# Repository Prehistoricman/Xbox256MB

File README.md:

# Xbox 256MB upgrade mod

Upgrade the original Xbox to quadruple its original RAM size. Why? Because we can. **For advanced modders only!** Understand the risks and drawbacks before attempting.

See [my tutorial on the OGXbox forums](https://www.ogxbox.com/forums/index.php?/topic/19155-256mb-ram-upgrade-release-and-tutorial/) or [Macho Nacho's tutorial on YouTube](https://www.youtube.com/watch?v=R2hvSL30Rlg).

# Xblast OS for RAM testing and flashing

See the [bitbucket downloads](https://bitbucket.org/prehistoricman/lpcmod_os/downloads/) and the [bitbucket readme](https://bitbucket.org/prehistoricman/lpcmod_os/src/master/README.md) for the RAM testing BIOS that lets you check each RAM chip individually.

# BIOS patching

Use Python 3 to run the patcher script BIOS_patcher_256MB.py. This patcher works on X2 and X3 BIOSes. Others not tested. Some BIOSes such as EvoX will run 256MB memory after applying this patch but will not be able to use the extra memory. They require additional patching.

Usage:

    python BIOS_patcher_256MB.py <BIOS file path> [-m] [-d]

The `-m` option will slow the RAM speed to 150MHz from the default of 200MHz. **I have found this is necessary on all my Xboxes to run 256MB stably.** You can recover some lost performance by overclocking the BIOS before applying the 256MB patch using a tool such as XBOverclock.

The `-d` option will attempt to adjust the slew and drive trims for the DQS pin. Try this if the system isn't stable.

This script will produce a patched version of the BIOS with `.patched256` appended to the name.

For example:

    python BIOS_patcher_256MB.py x2.5035.v16plus.137.bin -m

# Interposer PCB

This mod uses 256Mbit memory chips HY5DU573222F-28. They are only available in a BGA package, so we need an interposer to convert it to the Xbox's TQFP footprint.

PCB gerbers appropriate for PCBWay are in the github release.

256Mbit_RAM_interposer_v2_flex is my recommended design. It's intended to be manufactured in flexible PCB to be slim, easy to handle, and have enough outline precision to correctly make the castellated holes at the edge of the PCB. You can try ordering it in rigid fibreglass PCB but many manufacturers won't have the required tolerance on the board outline to avoid ripping the castellations apart.

256Mbit_RAM_interposer_rigidflex is my earlier design where the two inner layers are flexible and extend from the board, becoming pins and mimicing the original TQFP package. **This design suffers from the pins being too weak**: they get micro fractures from bending and therefore lose conductivity. This design would be ideal if the flexible layers could be on the bottom side of the board.

# Theory

This is just extra information for those who seek it.

See my video about this mod: [How I put 256MB of RAM in the original Xbox](https://www.youtube.com/watch?v=1idSEhUT4PM)

In short, we can double the memory from 128MB to 256MB by adding 1 more bit of addressing to the memory array. This is done by adding an additional 'column' since the Xbox is already maxed out on address 'rows'. To enable the use of that extra column bit, we have to write to the DRAM controller register called `NV_PFB_CFG1` in the Xbox's startup code (Xcodes). In the same register, we also have to set the AP pin to A9 to account for the flip of A8 and A9 in the interposer. Why are they flipped in the interposer? Because this DRAM controller unfortunately doesn't properly account for the location of the AP pin within the column address. The RAM chip accepts its column address on A0-A7+A9, skipping the A8 pin because its job is to be the AP pin. Instead, the NV2A uses A8 as the most significant bit in the column address (in 9 columns mode) and thus the function of the AP bit is lost and only half of memory is addressable.

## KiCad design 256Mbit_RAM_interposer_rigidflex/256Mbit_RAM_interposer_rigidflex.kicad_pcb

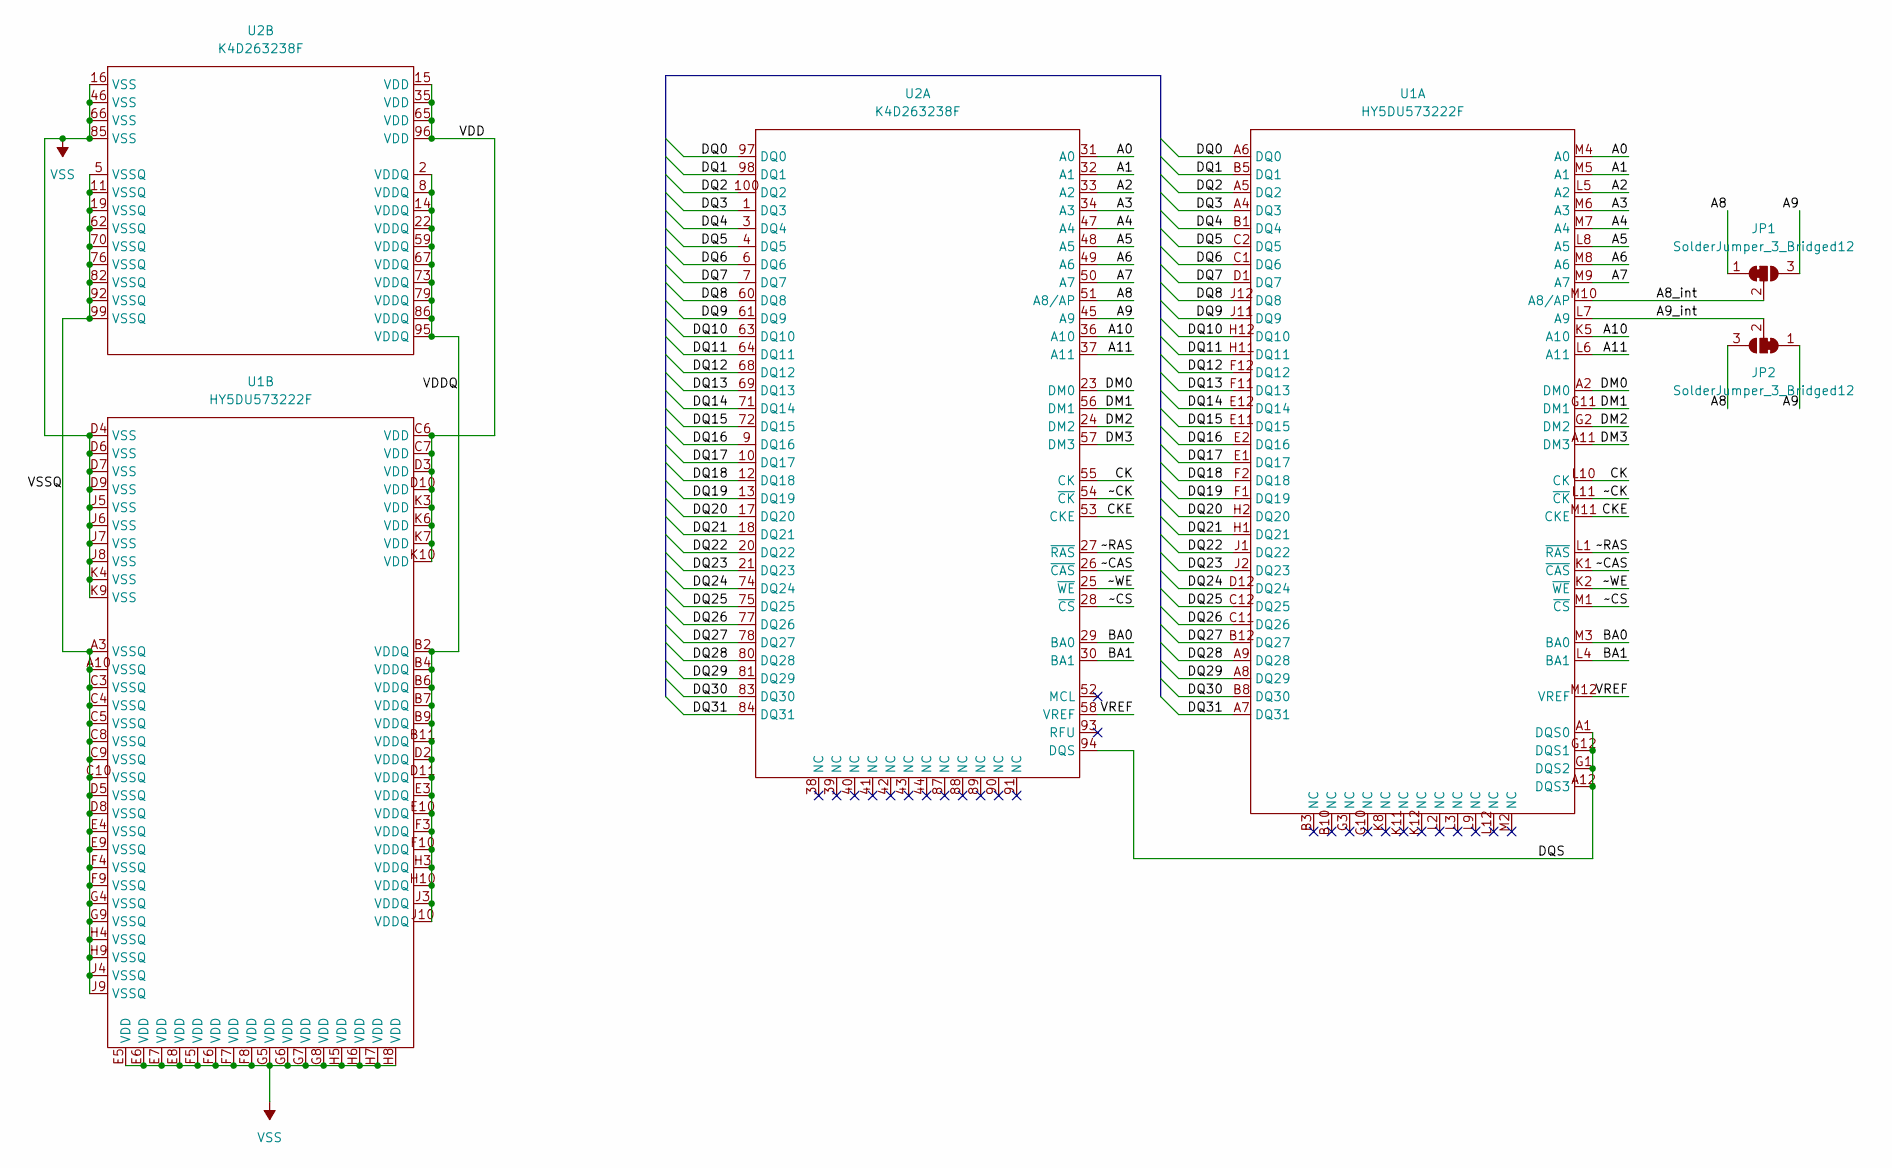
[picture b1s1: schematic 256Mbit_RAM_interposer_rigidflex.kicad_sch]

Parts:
JP1, JP2: SolderJumper_3_Bridged12; SolderJumper-3_P0.8mm_Open
U1: HY5DU573222F; LFBGA-144_10x10mm_Layout12x12_P0.8mm
U2: K4D263238F; PQFP-100_14x20mm_P0.65mm

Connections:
/A0: U1.M4 (A0), U2.31 (A0)
/A1: U1.M5 (A1), U2.32 (A1)
/A2: U1.L5 (A2), U2.33 (A2)
/A3: U1.M6 (A3), U2.34 (A3)
/A4: U1.M7 (A4), U2.47 (A4)
/A5: U1.L8 (A5), U2.48 (A5)
/A6: U1.M8 (A6), U2.49 (A6)
/A7: U1.M9 (A7), U2.50 (A7)
/A8: JP1.1 (A), JP2.3 (B), U2.51 (A8/AP)
/A8_int: JP1.2 (C), U1.M10 (A8/AP)
/A9: JP1.3 (B), JP2.1 (A), U2.45 (A9)
/A9_int: JP2.2 (C), U1.L7 (A9)
/A10: U1.K5 (A10), U2.36 (A10)
/A11: U1.L6 (A11), U2.37 (A11)
/BA0: U1.M3 (BA0), U2.29 (BA0)
/BA1: U1.L4 (BA1), U2.30 (BA1)
/CK: U1.L10 (CK), U2.55 (CK)
/CKE: U1.M11 (CKE), U2.53 (CKE)
/DM0: U1.A2 (DM0), U2.23 (DM0)
/DM1: U1.G11 (DM1), U2.56 (DM1)
/DM2: U1.G2 (DM2), U2.24 (DM2)
/DM3: U1.A11 (DM3), U2.57 (DM3)
/DQ0: U1.A6 (DQ0), U2.97 (DQ0)
/DQ1: U1.B5 (DQ1), U2.98 (DQ1)
/DQ2: U1.A5 (DQ2), U2.100 (DQ2)
/DQ3: U1.A4 (DQ3), U2.1 (DQ3)
/DQ4: U1.B1 (DQ4), U2.3 (DQ4)
/DQ5: U1.C2 (DQ5), U2.4 (DQ5)
/DQ6: U1.C1 (DQ6), U2.6 (DQ6)
/DQ7: U1.D1 (DQ7), U2.7 (DQ7)
/DQ8: U1.J12 (DQ8), U2.60 (DQ8)
/DQ9: U1.J11 (DQ9), U2.61 (DQ9)
/DQ10: U1.H12 (DQ10), U2.63 (DQ10)
/DQ11: U1.H11 (DQ11), U2.64 (DQ11)
/DQ12: U1.F12 (DQ12), U2.68 (DQ12)
/DQ13: U1.F11 (DQ13), U2.69 (DQ13)
/DQ14: U1.E12 (DQ14), U2.71 (DQ14)
/DQ15: U1.E11 (DQ15), U2.72 (DQ15)
/DQ16: U1.E2 (DQ16), U2.9 (DQ16)
/DQ17: U1.E1 (DQ17), U2.10 (DQ17)
/DQ18: U1.F2 (DQ18), U2.12 (DQ18)
/DQ19: U1.F1 (DQ19), U2.13 (DQ19)
/DQ20: U1.H2 (DQ20), U2.17 (DQ20)
/DQ21: U1.H1 (DQ21), U2.18 (DQ21)
/DQ22: U1.J1 (DQ22), U2.20 (DQ22)
/DQ23: U1.J2 (DQ23), U2.21 (DQ23)
/DQ24: U1.D12 (DQ24), U2.74 (DQ24)
/DQ25: U1.C12 (DQ25), U2.75 (DQ25)
/DQ26: U1.C11 (DQ26), U2.77 (DQ26)
/DQ27: U1.B12 (DQ27), U2.78 (DQ27)
/DQ28: U1.A9 (DQ28), U2.80 (DQ28)
/DQ29: U1.A8 (DQ29), U2.81 (DQ29)
/DQ30: U1.B8 (DQ30), U2.83 (DQ30)
/DQ31: U1.A7 (DQ31), U2.84 (DQ31)
/DQS: U1.A1 (DQS0), U1.A12 (DQS3), U1.G1 (DQS2), U1.G12 (DQS1), U2.94 (DQS)
/VDD: U1.C6 (VDD), U1.C7 (VDD), U1.D3 (VDD), U1.D10 (VDD), U1.K3 (VDD), U1.K6 (VDD), U1.K7 (VDD), U1.K10 (VDD), U2.15 (VDD), U2.35 (VDD), U2.65 (VDD), U2.96 (VDD)
/VDDQ: U1.B2 (VDDQ), U1.B4 (VDDQ), U1.B6 (VDDQ), U1.B7 (VDDQ), U1.B9 (VDDQ), U1.B11 (VDDQ), U1.D2 (VDDQ), U1.D11 (VDDQ), U1.E3 (VDDQ), U1.E10 (VDDQ), U1.F3 (VDDQ), U1.F10 (VDDQ), U1.H3 (VDDQ), U1.H10 (VDDQ), U1.J3 (VDDQ), U1.J10 (VDDQ), U2.2 (VDDQ), U2.8 (VDDQ), U2.14 (VDDQ), U2.22 (VDDQ), U2.59 (VDDQ), U2.67 (VDDQ), U2.73 (VDDQ), U2.79 (VDDQ), U2.86 (VDDQ), U2.95 (VDDQ)
/VREF: U1.M12 (VREF), U2.58 (VREF)
/VSSQ: U1.A3 (VSSQ), U1.A10 (VSSQ), U1.C3 (VSSQ), U1.C4 (VSSQ), U1.C5 (VSSQ), U1.C8 (VSSQ), U1.C9 (VSSQ), U1.C10 (VSSQ), U1.D5 (VSSQ), U1.D8 (VSSQ), U1.E4 (VSSQ), U1.E9 (VSSQ), U1.F4 (VSSQ), U1.F9 (VSSQ), U1.G4 (VSSQ), U1.G9 (VSSQ), U1.H4 (VSSQ), U1.H9 (VSSQ), U1.J4 (VSSQ), U1.J9 (VSSQ), U2.5 (VSSQ), U2.11 (VSSQ), U2.19 (VSSQ), U2.62 (VSSQ), U2.70 (VSSQ), U2.76 (VSSQ), U2.82 (VSSQ), U2.92 (VSSQ), U2.99 (VSSQ)
/~CAS: U1.K1 (~CAS), U2.26 (~CAS)
/~CK: U1.L11 (~CK), U2.54 (~CK)
/~CS: U1.M1 (~CS), U2.28 (~CS)
/~RAS: U1.L1 (~RAS), U2.27 (~RAS)
/~WE: U1.K2 (~WE), U2.25 (~WE)

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
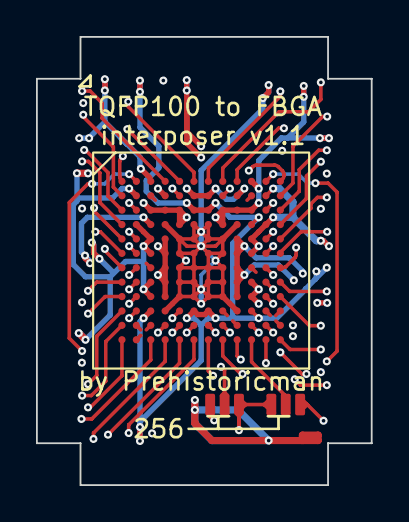
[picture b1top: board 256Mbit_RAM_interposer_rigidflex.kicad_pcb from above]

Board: 4 copper layers, 18.6 x 24.9 mm, 4 parts (0 on the bottom side), 65 nets.

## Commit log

2025-03-12 Initial commit 2
2025-03-13 Fix patcher for BIOSes which have the slews table shortly after xcodes
2025-03-15 Update PCBs
2025-03-15 Add PCB photos
2025-03-15 Add images to README.md
2025-05-15 Fix patcher for v1.6
    Now the patcher injects xcodes at the location where both 1.6 and pre-1.6 finish executing
